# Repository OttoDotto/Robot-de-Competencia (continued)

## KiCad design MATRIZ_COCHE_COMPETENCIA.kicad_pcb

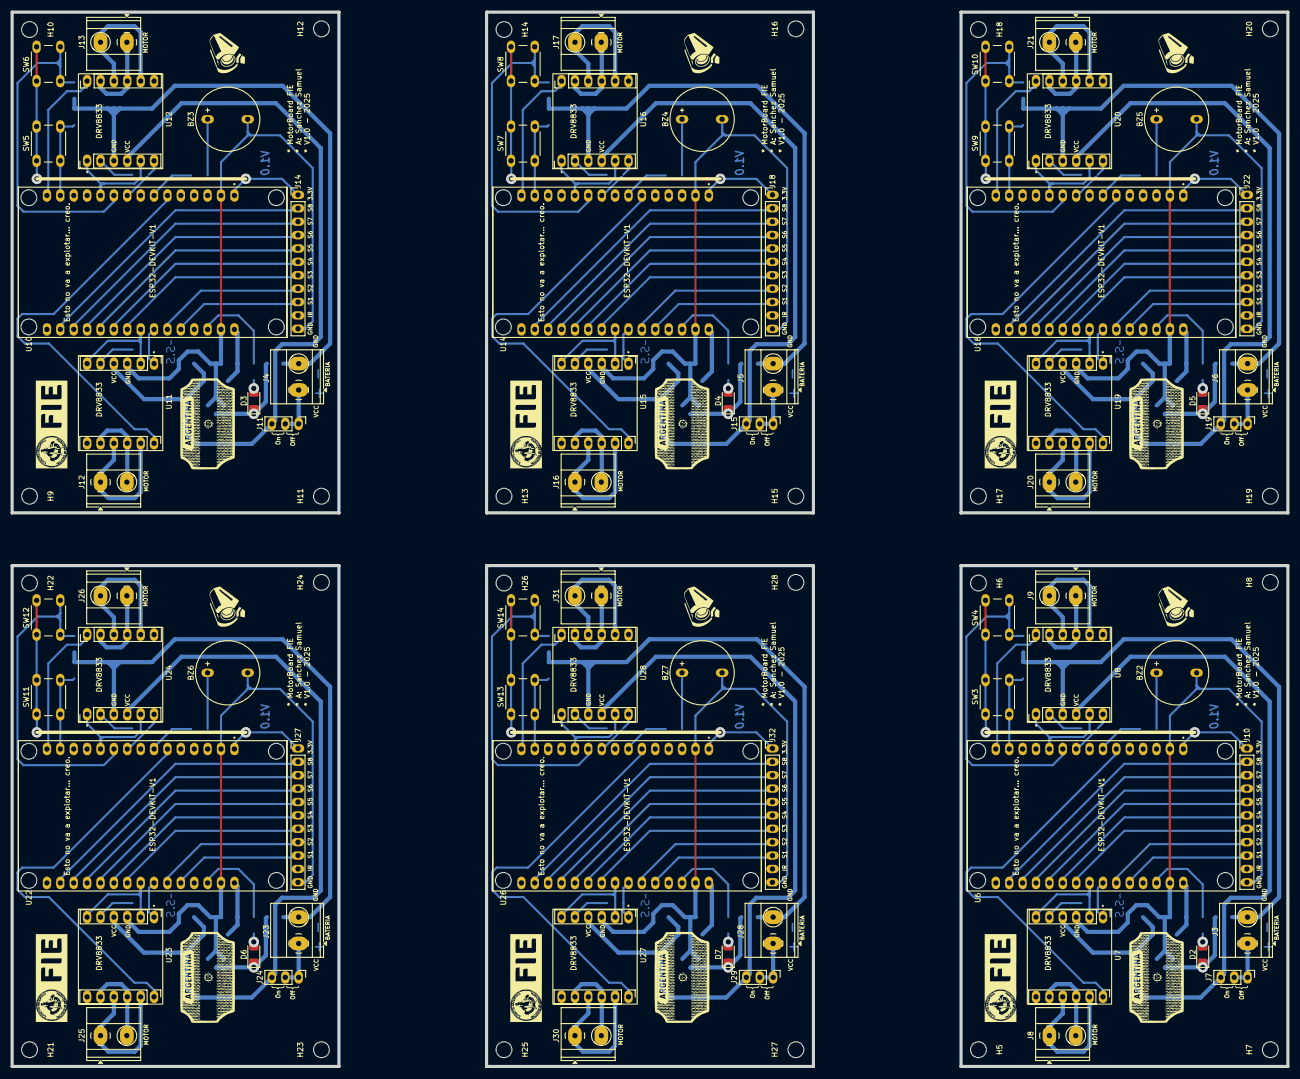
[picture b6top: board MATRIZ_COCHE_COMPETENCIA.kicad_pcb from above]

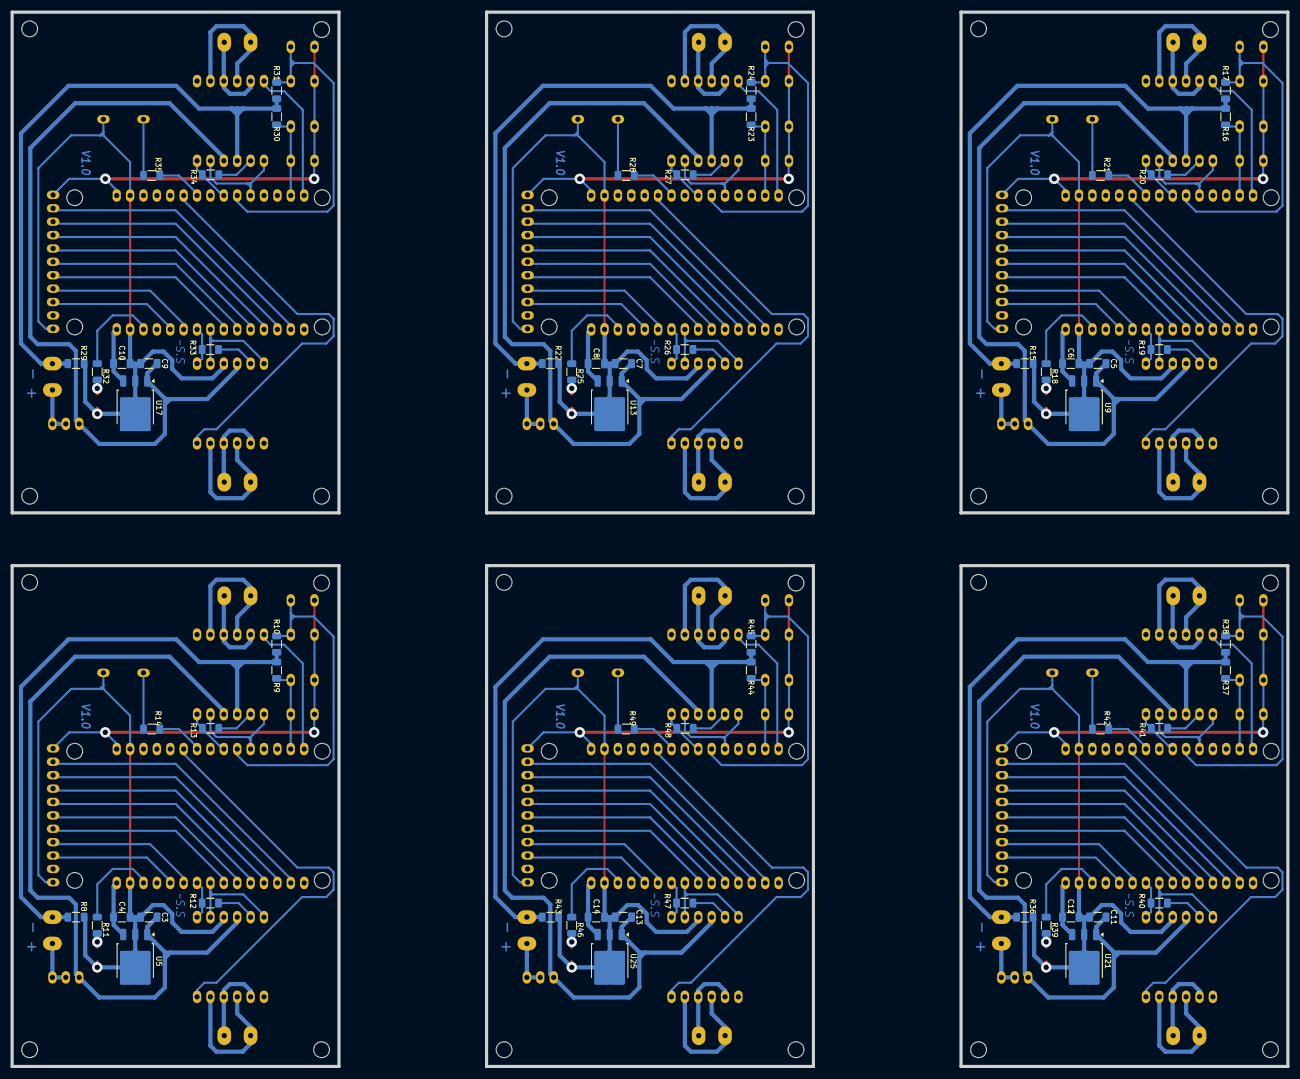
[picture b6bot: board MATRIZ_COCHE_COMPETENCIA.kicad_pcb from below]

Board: 2 copper layers, 242.0 x 200.0 mm, 156 parts (60 on the bottom side), 31 nets.

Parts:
BZ2, BZ3, BZ4, BZ5, BZ6, BZ7: Buzzer; MagneticBuzzer_ProSignal_ABI-009-RC
C3, C5, C7, C9, C11, C13: 0.33u; C_1206_3216Metric_Pad1.33x1.80mm_HandSolder
C4, C6, C8, C10, C12, C14: 0.1u; C_1206_3216Metric_Pad1.33x1.80mm_HandSolder
D2, D3, D4, D5, D6, D7: LED_RED; LED_1206_3216Metric_Pad1.42x1.75mm_HandSolder
H5, H6, H7, H8, H9, H10, H11, H12, H13, H14, H15, H16, H17, H18, H19, H20, H21, H22, H23, H24, H25, H26, H27, H28: MountingHole; MountingHole_3mm
J3, J4, J5, J6, J23, J28: BAT; TerminalBlock_Phoenix_MKDS-1,5-2_1x02_P5.00mm_Horizontal
J7, J11, J15, J19, J24, J29: SWITCH; PinHeader_1x03_P2.54mm_Vertical
J8, J12, J16, J20, J25, J30: M1; TerminalBlock_Phoenix_MKDS-1,5-2_1x02_P5.00mm_Horizontal
J9, J13, J17, J21, J26, J31: M2; TerminalBlock_Phoenix_MKDS-1,5-2_1x02_P5.00mm_Horizontal
J10, J14, J18, J22, J27, J32: SENSORES; PinHeader_1x11_P2.54mm_Vertical
R8, R12, R13, R14, R15, R19, R20, R21, R22, R26, R27, R28, R29, R33, R34, R35, R36, R40, R41, R42, R43, R47, R48, R49: 0; R_1206_3216Metric_Pad1.30x1.75mm_HandSolder
R9, R10, R16, R17, R23, R24, R30, R31, R37, R38, R44, R45: 10k; R_1206_3216Metric_Pad1.30x1.75mm_HandSolder
R11, R18, R25, R32, R39, R46: 220; R_1206_3216Metric_Pad1.30x1.75mm_HandSolder
SW3, SW4, SW5, SW6, SW7, SW8, SW9, SW10, SW11, SW12, SW13, SW14: SW_Push; SW_PUSH_6mm_H5mm
U5, U9, U13, U17, U21, U25: L7805; TO-252-3_TabPin2
U6, U10, U14, U18, U22, U26: ESP32-DEVKIT-V1; MODULE_ESP32_DEVKIT_V1
U7, U8, U11, U12, U15, U16, U19, U20, U23, U24, U27, U28: DRV8833

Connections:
+3.3V: J10.1, J14.1, J18.1, J22.1, J27.1, J32.1, SW3.1, SW4.1, SW5.1, SW6.1, SW7.1, SW8.1, SW9.1, SW10.1, SW11.1, SW12.1, SW13.1, SW14.1, U6.1 (3V3), U10.1 (3V3), U14.1 (3V3), U18.1 (3V3), U22.1 (3V3), U26.1 (3V3)
+5V: C4.1, C6.1, C8.1, C10.1, C12.1, C14.1, U5.3 (OUT), U6.30 (VIN), U9.3 (OUT), U10.30 (VIN), U13.3 (OUT), U14.30 (VIN), U17.3 (OUT), U18.30 (VIN), U21.3 (OUT), U22.30 (VIN), U25.3 (OUT), U26.30 (VIN)
/BUZZER: R14.1, R21.1, R28.1, R35.1, R42.1, R49.1, U6.7 (TX2), U10.7 (TX2), U14.7 (TX2), U18.7 (TX2), U22.7 (TX2), U26.7 (TX2)
/IN_M1_A: R12.1, R19.1, R26.1, R33.1, R40.1, R47.1, U6.24 (D26), U7.1 (IN4), U10.24 (D26), U11.1 (IN4), U14.24 (D26), U15.1 (IN4), U18.24 (D26), U19.1 (IN4), U22.24 (D26), U23.1 (IN4), U26.24 (D26), U27.1 (IN4)
/IN_M1_B: U6.23 (D25), U7.2 (IN3), U7.6 (IN1), U10.23 (D25), U11.2 (IN3), U11.6 (IN1), U14.23 (D25), U15.2 (IN3), U15.6 (IN1), U18.23 (D25), U19.2 (IN3), U19.6 (IN1), U22.23 (D25), U23.2 (IN3), U23.6 (IN1), U26.23 (D25), U27.2 (IN3), U27.6 (IN1)
/IN_M2_A: U6.11 (D21), U8.1 (IN4), U8.5 (IN2), U10.11 (D21), U12.1 (IN4), U12.5 (IN2), U14.11 (D21), U16.1 (IN4), U16.5 (IN2), U18.11 (D21), U20.1 (IN4), U20.5 (IN2), U22.11 (D21), U24.1 (IN4), U24.5 (IN2), U26.11 (D21), U28.1 (IN4), U28.5 (IN2)
/IN_M2_B: R13.1, R20.1, R27.1, R34.1, R41.1, R48.1, U6.9 (D18), U8.6 (IN1), U10.9 (D18), U12.6 (IN1), U14.9 (D18), U16.6 (IN1), U18.9 (D18), U20.6 (IN1), U22.9 (D18), U24.6 (IN1), U26.9 (D18), U28.6 (IN1)
/LED_LARGADA: R11.1, R18.1, R25.1, R32.1, R39.1, R46.1, U6.28 (D13), U10.28 (D13), U14.28 (D13), U18.28 (D13), U22.28 (D13), U26.28 (D13)
/S1: J10.9, J14.9, J18.9, J22.9, J27.9, J32.9, U6.26 (D14), U10.26 (D14), U14.26 (D14), U18.26 (D14), U22.26 (D14), U26.26 (D14)
/S2: J10.8, J14.8, J18.8, J22.8, J27.8, J32.8, U6.25 (D27), U10.25 (D27), U14.25 (D27), U18.25 (D27), U22.25 (D27), U26.25 (D27)
/S3: J10.7, J14.7, J18.7, J22.7, J27.7, J32.7, U6.22 (D33), U10.22 (D33), U14.22 (D33), U18.22 (D33), U22.22 (D33), U26.22 (D33)
/S4: J10.6, J14.6, J18.6, J22.6, J27.6, J32.6, U6.21 (D32), U10.21 (D32), U14.21 (D32), U18.21 (D32), U22.21 (D32), U26.21 (D32)
/S5: J10.5, J14.5, J18.5, J22.5, J27.5, J32.5, U6.20 (D35), U10.20 (D35), U14.20 (D35), U18.20 (D35), U22.20 (D35), U26.20 (D35)
/S6: J10.4, J14.4, J18.4, J22.4, J27.4, J32.4, U6.19 (D34), U10.19 (D34), U14.19 (D34), U18.19 (D34), U22.19 (D34), U26.19 (D34)
/S7: J10.3, J14.3, J18.3, J22.3, J27.3, J32.3, U6.18 (VN), U10.18 (VN), U14.18 (VN), U18.18 (VN), U22.18 (VN), U26.18 (VN)
/S8: J10.2, J14.2, J18.2, J22.2, J27.2, J32.2, U6.17 (VP), U10.17 (VP), U14.17 (VP), U18.17 (VP), U22.17 (VP), U26.17 (VP)
/SLEEP_M1: U6.6 (RX2), U7.12 (SLEEP), U10.6 (RX2), U11.12 (SLEEP), U14.6 (RX2), U15.12 (SLEEP), U18.6 (RX2), U19.12 (SLEEP), U22.6 (RX2), U23.12 (SLEEP), U26.6 (RX2), U27.12 (SLEEP)
/SLEEP_M2: U6.15 (D23), U8.12 (SLEEP), U10.15 (D23), U12.12 (SLEEP), U14.15 (D23), U16.12 (SLEEP), U18.15 (D23), U20.12 (SLEEP), U22.15 (D23), U24.12 (SLEEP), U26.15 (D23), U28.12 (SLEEP)
/SW1: R9.1, R16.1, R23.1, R30.1, R37.1, R44.1, SW3.2, SW5.2, SW7.2, SW9.2, SW11.2, SW13.2, U6.14 (D22), U10.14 (D22), U14.14 (D22), U18.14 (D22), U22.14 (D22), U26.14 (D22)
/SW2: R10.1, R17.1, R24.1, R31.1, R38.1, R45.1, SW4.2, SW6.2, SW8.2, SW10.2, SW12.2, SW14.2, U6.10 (D19), U10.10 (D19), U14.10 (D19), U18.10 (D19), U22.10 (D19), U26.10 (D19)
GND: BZ2.2 (-), BZ3.2 (-), BZ4.2 (-), BZ5.2 (-), BZ6.2 (-), BZ7.2 (-), C3.2, C4.2, C5.2, C6.2, C7.2, C8.2, C9.2, C10.2, C11.2, C12.2, C13.2, C14.2, D2.1 (K), D3.1 (K), D4.1 (K), D5.1 (K), D6.1 (K), D7.1 (K), J3.2, J4.2, J5.2, J6.2, J10.11, J14.11, J18.11, J22.11, J23.2, J27.11, J28.2, J32.11, R8.1, R8.2, R9.2, R10.2, R15.1, R15.2, R16.2, R17.2, R22.1, R22.2, R23.2, R24.2, R29.1, R29.2, R30.2, R31.2, R36.1, R36.2, R37.2, R38.2, R43.1, R43.2, R44.2, R45.2, U5.2 (GND), U6.2 (GND), U6.29 (GND), U7.3 (GND), U8.3 (GND), U9.2 (GND), U10.2 (GND), U10.29 (GND), U11.3 (GND), U12.3 (GND), U13.2 (GND), U14.2 (GND), U14.29 (GND), U15.3 (GND), U16.3 (GND), U17.2 (GND), U18.2 (GND), U18.29 (GND), U19.3 (GND), U20.3 (GND), U21.2 (GND), U22.2 (GND), U22.29 (GND), U23.3 (GND), U24.3 (GND), U25.2 (GND), U26.2 (GND), U26.29 (GND), U27.3 (GND), U28.3 (GND)
unnamed: BZ2.1 (+), BZ3.1 (+), BZ4.1 (+), BZ5.1 (+), BZ6.1 (+), BZ7.1 (+), R14.2, R21.2, R28.2, R35.2, R42.2, R49.2
unnamed: D2.2 (A), D3.2 (A), D4.2 (A), D5.2 (A), D6.2 (A), D7.2 (A), R11.2, R18.2, R25.2, R32.2, R39.2, R46.2
unnamed: J3.1, J4.1, J5.1, J6.1, J7.1, J7.2, J11.1, J11.2, J15.1, J15.2, J19.1, J19.2, J23.1, J24.1, J24.2, J28.1, J29.1, J29.2
unnamed: J8.1, J12.1, J16.1, J20.1, J25.1, J30.1, U7.9 (OUT3), U7.11 (OUT1), U11.9 (OUT3), U11.11 (OUT1), U15.9 (OUT3), U15.11 (OUT1), U19.9 (OUT3), U19.11 (OUT1), U23.9 (OUT3), U23.11 (OUT1), U27.9 (OUT3), U27.11 (OUT1)
unnamed: J8.2, J12.2, J16.2, J20.2, J25.2, J30.2, U7.8 (OUT4), U7.10 (OUT2), U11.8 (OUT4), U11.10 (OUT2), U15.8 (OUT4), U15.10 (OUT2), U19.8 (OUT4), U19.10 (OUT2), U23.8 (OUT4), U23.10 (OUT2), U27.8 (OUT4), U27.10 (OUT2)
unnamed: J9.1, J13.1, J17.1, J21.1, J26.1, J31.1, U8.9 (OUT3), U8.11 (OUT1), U12.9 (OUT3), U12.11 (OUT1), U16.9 (OUT3), U16.11 (OUT1), U20.9 (OUT3), U20.11 (OUT1), U24.9 (OUT3), U24.11 (OUT1), U28.9 (OUT3), U28.11 (OUT1)
unnamed: J9.2, J13.2, J17.2, J21.2, J26.2, J31.2, U8.8 (OUT4), U8.10 (OUT2), U12.8 (OUT4), U12.10 (OUT2), U16.8 (OUT4), U16.10 (OUT2), U20.8 (OUT4), U20.10 (OUT2), U24.8 (OUT4), U24.10 (OUT2), U28.8 (OUT4), U28.10 (OUT2)
unnamed: R12.2, R19.2, R26.2, R33.2, R40.2, R47.2, U7.5 (IN2), U11.5 (IN2), U15.5 (IN2), U19.5 (IN2), U23.5 (IN2), U27.5 (IN2)
unnamed: R13.2, R20.2, R27.2, R34.2, R41.2, R48.2, U8.2 (IN3), U12.2 (IN3), U16.2 (IN3), U20.2 (IN3), U24.2 (IN3), U28.2 (IN3)
VCC: C3.1, C5.1, C7.1, C9.1, C11.1, C13.1, J7.3, J11.3, J15.3, J19.3, J24.3, J29.3, U5.1 (IN), U7.4 (VCC), U8.4 (VCC), U9.1 (IN), U11.4 (VCC), U12.4 (VCC), U13.1 (IN), U15.4 (VCC), U16.4 (VCC), U17.1 (IN), U19.4 (VCC), U20.4 (VCC), U21.1 (IN), U23.4 (VCC), U24.4 (VCC), U25.1 (IN), U27.4 (VCC), U28.4 (VCC)

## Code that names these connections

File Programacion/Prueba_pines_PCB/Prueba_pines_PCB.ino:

/*
* PINES ESP32 ELEJIDOS:	(D = GPIO !!!!)
Sensores (fila bajo el USB, contiguos para pistas rectas)
S1 → GPIO36 (VP)
S2 → GPIO39 (VN)
S3 → GPIO34
S4 → GPIO35
S5 → GPIO32
S6 → GPIO33
S7 → GPIO27
S8 → GPIO14

Puente H izquierdo (M1) – lado izquierdo del ESP32
IN1_M1 → GPIO26 (PWM)
IN2_M1 → GPIO25 (PWM)
SLEEP_M1 → GPIO16

Puente H derecho (M2) – lado derecho del ESP32
IN1_M2 → GPIO21 (PWM)
IN2_M2 → GPIO18 (PWM)
SLEEP_M2 → GPIO23

Botones, buzzer, LED (abajo/derecha)
SW1 → GPIO22 (entrada con pull-up interno)
SW2 → GPIO19 (entrada con pull-up interno)
BUZZER → GPIO17 (PWM con LEDC)			(PROBLEMA, queda atrapado)
LED → GPIO13 (salida)
*/

// Sensores (solo lectura, ADC)
int sensores[] = {36, 39, 34, 35, 32, 33, 27, 14};
int totalSensores = sizeof(sensores) / sizeof(sensores[0]);

// Motores (IN1, IN2, SLEEP)
int motor1[] = {26, 25, 16}; // IN1, IN2, SLEEP
int motor2[] = {21, 18, 23}; // IN1, IN2, SLEEP

// Botones
int botones[] = {22, 19};
int totalBotones = sizeof(botones) / sizeof(botones[0]);

// Periféricos simples
int BUZZER = 17;
int LED = 13;

void setup() {
  Serial.begin(115200);
  Serial.println("Test PCB - ESP32 (arrays)");

  // Sensores
  for (int i = 0; i < totalSensores; i++) {
    pinMode(sensores[i], INPUT);
  }

  // Motores
  for (int i = 0; i < 3; i++) {
    pinMode(motor1[i], OUTPUT);
    pinMode(motor2[i], OUTPUT);
  }

  // Botones
  for (int i = 0; i < totalBotones; i++) {
    pinMode(botones[i], INPUT_PULLUP);
  }

  // Periféricos
  pinMode(BUZZER, OUTPUT);
  pinMode(LED, OUTPUT);
}

void loop() {
  // Sensores
  Serial.print("Sensores: ");
  for (int i = 0; i < totalSensores; i++) {
    Serial.print(analogRead(sensores[i]));
    Serial.print(" ");
  }
  Serial.println();

  // Botones
  Serial.print("Botones: ");
  for (int i = 0; i < totalBotones; i++) {
    Serial.print(digitalRead(botones[i]));
    Serial.print(" ");
  }
  Serial.println();

  // Motores: cambiar estado simple
  digitalWrite(motor1[2], HIGH); // SLEEP_M1
  digitalWrite(motor2[2], HIGH); // SLEEP_M2

  digitalWrite(motor1[0], HIGH); digitalWrite(motor1[1], LOW);
  digitalWrite(motor2[0], HIGH); digitalWrite(motor2[1], LOW);
  delay(300);
  digitalWrite(motor1[0], LOW); digitalWrite(motor1[1], HIGH);
  digitalWrite(motor2[0], LOW); digitalWrite(motor2[1], HIGH);
  delay(300);

  // LED y buzzer
  digitalWrite(LED, HIGH);
  digitalWrite(BUZZER, HIGH);
  delay(100);
  digitalWrite(LED, LOW);
  digitalWrite(BUZZER, LOW);
  delay(100);
}

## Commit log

2025-08-25 V1 - Primer commit.
2025-08-28 V1 - MotorBoard 2025
2025-08-28 V1.0 - Modelo 3D.
2025-08-31 Added Coche de Competencia.drawio
2025-08-31 Added Coche.drawio
2025-08-31 V1 - Diagrama Draw.io y Mejoras documentacion
2025-08-31 V1 - Reestructuracion de carpetas + incorporacion de galeria
2025-08-31 Rename README.txt to README.md
2025-09-04 V1.1 - Correccion de bocina y programas de motores.
2025-09-04 V1.1 - Programa de Buzzer + Modulo Drv8833
2025-09-04 V1.1 - Reordenamiento de carpetas
2025-09-09 V1.2 - Mejoras de PCB: alimentacion, bocina y borneras.
2025-09-09 Add files via upload
    Prueba de Sensores - 09Sep25
2025-09-09 Primer commit: sensores y motores
2025-09-10 V1.3 - Diodo de proteccion + Mejor ubicacion de Sw's
2025-09-14 V1.3 - Agregado de Prot. Tension inversa & pull downs y acomodado de componentes.
2025-09-24 V1.3 - Protecciones
2025-09-24 BaronRojo prueba del 23Sep25
    Prueba de código base en funcionamiento
2025-10-01 V1.4 - Mejores pistas & Modulo de Interrupciones
2025-10-01 Nightfall Runner V0.1
2025-10-02 V1.5 - Ajuste PID adaptativo
2025-10-02 V1.5 - Ajuste PID adaptativo y controlado mediante ESP-NOW
2025-10-03 Nightfall Condor - Ajustar PID, flujo de programa y bocina/calibracion
2025-10-04 Nightfall Condor - Flujo y Bocina TODO modulo pid.
2025-10-04 Nightfall Condor - PID precompetencia.
2025-10-07 Nightfall Condor PreComp - Varios errores.
2025-10-17 V1.4 - Programa PID seguidor
2025-10-29 V1.4 - Programa seguidor Modular
2026-03-01 V1.5 - Pre_2026
2026-03-19 V2.0 - Nueva version Seguidor De Linea
2026-03-20 Agregado de Pcb Futboleros V1.5
